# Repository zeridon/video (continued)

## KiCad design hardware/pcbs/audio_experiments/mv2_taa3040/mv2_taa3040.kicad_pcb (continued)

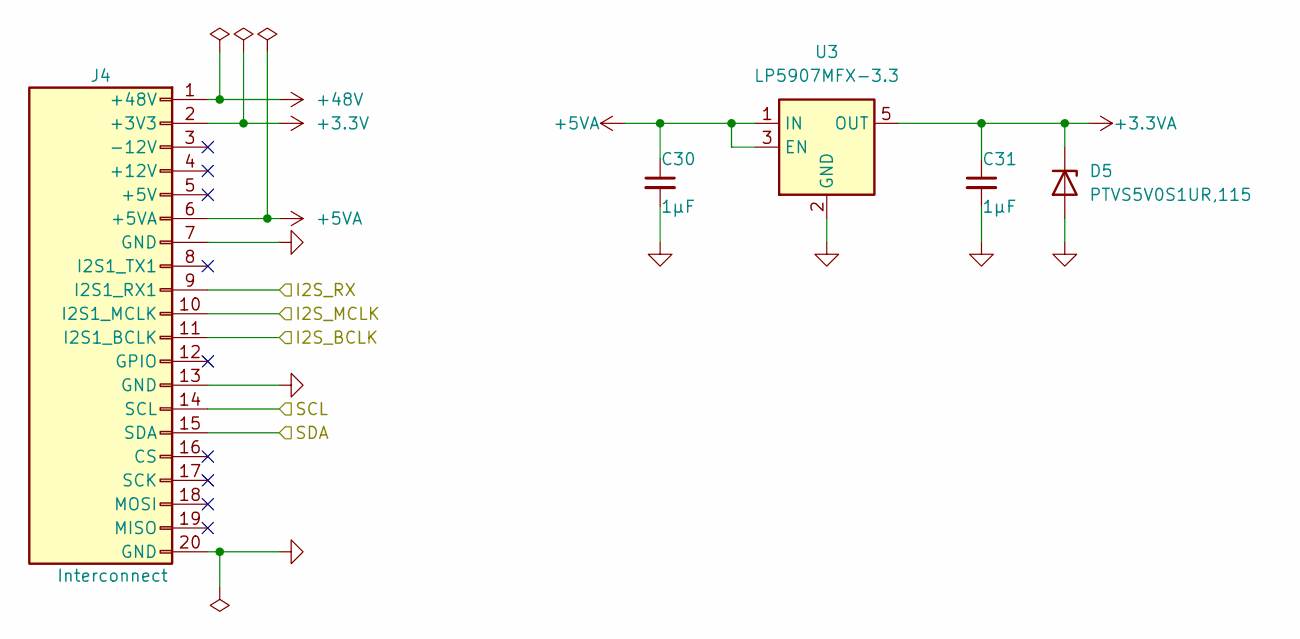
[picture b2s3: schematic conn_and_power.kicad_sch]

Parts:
C30, C31: 1μF; C_0805_2012Metric; MPN C 1μF 16V 0805
D5: PTVS5V0S1UR,115; Nexperia_CFP3_SOD-123W; MPN PTVS5V0S1UR,115; LCSC C478011
J4: Interconnect; PinHeader_1x20_P2.54mm_Vertical; MPN Header_1x20
U3: LP5907MFX-3.3; SOT-23-5; MPN LP5907MFX-3.3; LCSC C80670

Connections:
+3.3V: J4.2 (+3V3); also elsewhere on the board
+3.3VA: C31.1, D5.1 (K), U3.5 (OUT); also elsewhere on the board
+5VA: C30.1, J4.6 (+5VA), U3.1 (IN), U3.3 (EN)
+48V: J4.1 (+48V); also elsewhere on the board
/Conn and power/I2S_BCLK: J4.11 (I2S1_BCLK); also elsewhere on the board
/Conn and power/I2S_MCLK: J4.10 (I2S1_MCLK); also elsewhere on the board
/Conn and power/I2S_RX: J4.9 (I2S1_RX1); also elsewhere on the board
/Conn and power/SCL: J4.14 (SCL); also elsewhere on the board
/Conn and power/SDA: J4.15 (SDA); also elsewhere on the board
GND: C30.2, C31.2, D5.2 (A), J4.7 (GND), J4.13 (GND), J4.20 (GND), U3.2 (GND); also elsewhere on the board

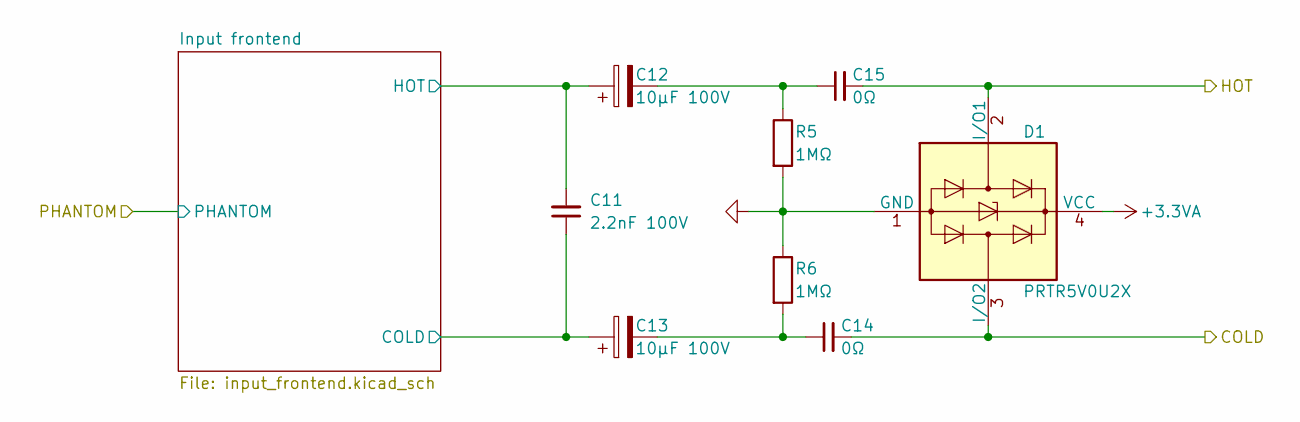
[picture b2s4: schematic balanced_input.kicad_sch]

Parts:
C11: 2.2nF 100V; C_0805_2012Metric; MPN C 2.2nF 100V 0805
C12, C13: 10μF 100V; CP_Radial_D5.0mm_P2.00mm; MPN C 10μF 100V P2
C14: 0Ω; C_1206_3216Metric; MPN R 0Ω 1206
C15: 0Ω; C_1206_3216Metric; MPN R 0Ω 0805
D1: PRTR5V0U2X; SOT-143; MPN PRTR5V0U2X,215; LCSC C12333
R5, R6: 1MΩ; R_0603_1608Metric; MPN 1MΩ 125mW 5% 0603

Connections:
+3.3VA: D1.4 (VCC); also elsewhere on the board
/Balanced Input 1/COLD: C14.2, D1.3 (I/O2); also elsewhere on the board
/Balanced Input 1/HOT: C15.2, D1.2 (I/O1); also elsewhere on the board
/Balanced Input 1/Input frontend/COLD: C11.1, C13.1; also elsewhere on the board
/Balanced Input 1/Input frontend/HOT: C11.2, C12.1; also elsewhere on the board
GND: D1.1 (GND), R5.2, R6.1; also elsewhere on the board
unnamed: C12.2, C15.1, R5.1
unnamed: C13.2, C14.1, R6.2

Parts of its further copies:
C16: 2.2nF 100V; C_0805_2012Metric; MPN C 2.2nF 100V 0805
C17, C18: 10μF 100V; CP_Radial_D5.0mm_P2.00mm; MPN C 10μF 100V P2
C19: 0Ω; C_1206_3216Metric; MPN R 0Ω 1206
C20: 0Ω; C_1206_3216Metric; MPN R 0Ω 0805
D2: PRTR5V0U2X; SOT-143; MPN PRTR5V0U2X,215; LCSC C12333
R7, R8: 1MΩ; R_0603_1608Metric; MPN 1MΩ 125mW 5% 0603

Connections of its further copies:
+3.3VA: D2.4 (VCC); also elsewhere on the board
/Balanced Input 2/COLD: C19.2, D2.3 (I/O2); also elsewhere on the board
/Balanced Input 2/HOT: C20.2, D2.2 (I/O1); also elsewhere on the board
/Balanced Input 2/Input frontend/COLD: C16.1, C18.1; also elsewhere on the board
/Balanced Input 2/Input frontend/HOT: C16.2, C17.1; also elsewhere on the board
GND: D2.1 (GND), R7.2, R8.1; also elsewhere on the board
unnamed: C17.2, C20.1, R7.1
unnamed: C18.2, C19.1, R8.2

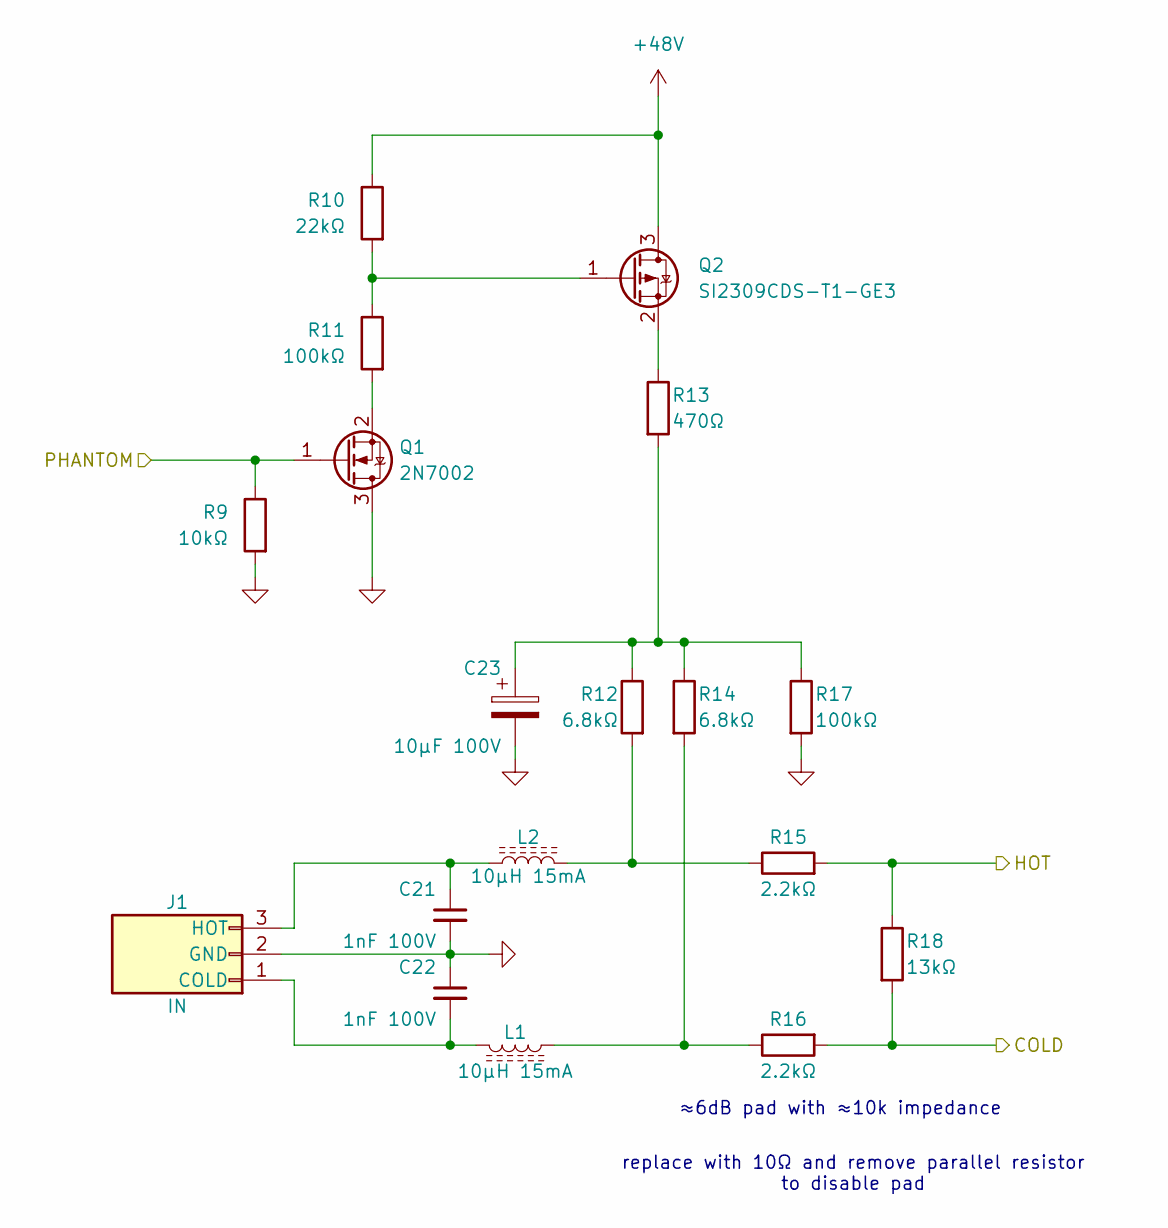
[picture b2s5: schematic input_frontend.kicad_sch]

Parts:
C21, C22: 1nF 100V; C_0805_2012Metric; MPN C 1nF 100V 0805
C23: 10μF 100V; CP_Radial_D5.0mm_P2.00mm; MPN C 10μF 100V P2
J1: MTA100-3; mta100_01x3_P2.54_640455-3; MPN 640457-3
L1, L2: 10μH 15mA; L_0805_2012Metric; MPN SDFL1608S100KTF or LQM21FN100N00L; LCSC C1046
Q1: 2N7002; SOT-23; Part 2N7002; LCSC C8545
Q2: SI2309CDS-T1-GE3; SOT-23; MPN SI2309CDS-T1-GE3
R9: 10kΩ; R_0603_1608Metric; MPN R 10kΩ 125mW 5% 0603
R10: 22kΩ; R_0603_1608Metric; MPN R 22kΩ 125mW 5% 0603
R11, R17: 100kΩ; R_0603_1608Metric; MPN R 100kΩ 125mW 5% 0603
R12, R14: 6.8kΩ; R_0603_1608Metric; MPN R 6.8kΩ 125mW 1% 0603
R13: 470Ω; R_0603_1608Metric; MPN R 470Ω 125mW 5% 0603
R15, R16: 2.2kΩ; R_0603_1608Metric; MPN R 2.2kΩ 125mW 1% 0603
R18: 13kΩ; R_0603_1608Metric; MPN R 13kΩ 125mW 1% 0603

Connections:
+48V: Q2.3 (D), R10.1; also elsewhere on the board
/Balanced Input 3/Input frontend/COLD: R16.2, R18.2; also elsewhere on the board
/Balanced Input 3/Input frontend/HOT: R15.2, R18.1; also elsewhere on the board
/Balanced Input 3/PHANTOM: Q1.1 (G), R9.1; also elsewhere on the board
GND: C21.2, C22.1, C23.2, J1.2, Q1.3 (D), R9.2, R17.2; also elsewhere on the board
unnamed: C23.1, R12.1, R13.2, R14.1, R17.1
unnamed: C22.2, J1.1, L1.1
unnamed: C21.1, J1.3, L2.1
unnamed: L1.2, R14.2, R16.1
unnamed: L2.2, R12.2, R15.1
unnamed: Q1.2 (S), R11.2
unnamed: Q2.1 (G), R10.2, R11.1
unnamed: Q2.2 (S), R13.1

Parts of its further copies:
C24, C25, C27, C28, C32, C33: 1nF 100V; C_0805_2012Metric; MPN C 1nF 100V 0805
C26, C29, C34: 10μF 100V; CP_Radial_D5.0mm_P2.00mm; MPN C 10μF 100V P2
J2, J3, J5: MTA100-3; mta100_01x3_P2.54_640455-3; MPN 640457-3
L3, L4, L5, L6, L7, L8: 10μH 15mA; L_0805_2012Metric; MPN SDFL1608S100KTF or LQM21FN100N00L; LCSC C1046
Q3, Q5, Q7: 2N7002; SOT-23; Part 2N7002; LCSC C8545
Q4, Q6, Q8: SI2309CDS-T1-GE3; SOT-23; MPN SI2309CDS-T1-GE3
R19, R29, R39: 10kΩ; R_0603_1608Metric; MPN R 10kΩ 125mW 5% 0603
R20, R30, R40: 22kΩ; R_0603_1608Metric; MPN R 22kΩ 125mW 5% 0603
R21, R27, R31, R37, R41, R47: 100kΩ; R_0603_1608Metric; MPN R 100kΩ 125mW 5% 0603
R22, R24, R32, R34, R42, R44: 6.8kΩ; R_0603_1608Metric; MPN R 6.8kΩ 125mW 1% 0603
R23, R33, R43: 470Ω; R_0603_1608Metric; MPN R 470Ω 125mW 5% 0603
R25, R26, R35, R36, R45, R46: 2.2kΩ; R_0603_1608Metric; MPN R 2.2kΩ 125mW 1% 0603
R28, R38, R48: 13kΩ; R_0603_1608Metric; MPN R 13kΩ 125mW 1% 0603

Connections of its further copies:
+48V: Q4.3 (D), Q6.3 (D), Q8.3 (D), R20.1, R30.1, R40.1; also elsewhere on the board
/Balanced Input 1/Input frontend/COLD: R46.2, R48.2; also elsewhere on the board
/Balanced Input 1/Input frontend/HOT: R45.2, R48.1; also elsewhere on the board
/Balanced Input 1/PHANTOM: Q7.1 (G), R39.1; also elsewhere on the board
/Balanced Input 2/Input frontend/COLD: R26.2, R28.2; also elsewhere on the board
/Balanced Input 2/Input frontend/HOT: R25.2, R28.1; also elsewhere on the board
/Balanced Input 2/PHANTOM: Q3.1 (G), R19.1; also elsewhere on the board
/Balanced Input 4/Input frontend/COLD: R36.2, R38.2; also elsewhere on the board
/Balanced Input 4/Input frontend/HOT: R35.2, R38.1; also elsewhere on the board
/Balanced Input 4/PHANTOM: Q5.1 (G), R29.1; also elsewhere on the board
GND: C24.2, C25.1, C26.2, C27.2, C28.1, C29.2, C32.2, C33.1, C34.2, J2.2, J3.2, J5.2, Q3.3 (D), Q5.3 (D), Q7.3 (D), R19.2, R27.2, R29.2, R37.2, R39.2, R47.2; also elsewhere on the board
unnamed: C26.1, R22.1, R23.2, R24.1, R27.1
unnamed: C29.1, R32.1, R33.2, R34.1, R37.1
unnamed: C34.1, R42.1, R43.2, R44.1, R47.1
unnamed: C25.2, J2.1, L3.1
unnamed: C24.1, J2.3, L4.1
unnamed: C28.2, J3.1, L5.1
unnamed: C27.1, J3.3, L6.1
unnamed: C33.2, J5.1, L7.1
unnamed: C32.1, J5.3, L8.1
unnamed: L3.2, R24.2, R26.1
unnamed: L4.2, R22.2, R25.1
unnamed: L5.2, R34.2, R36.1
unnamed: L6.2, R32.2, R35.1
unnamed: L7.2, R44.2, R46.1
unnamed: L8.2, R42.2, R45.1
unnamed: Q3.2 (S), R21.2
unnamed: Q4.1 (G), R20.2, R21.1
unnamed: Q4.2 (S), R23.1
unnamed: Q5.2 (S), R31.2
unnamed: Q6.1 (G), R30.2, R31.1
unnamed: Q6.2 (S), R33.1
unnamed: Q7.2 (S), R41.2
unnamed: Q8.1 (G), R40.2, R41.1
unnamed: Q8.2 (S), R43.1

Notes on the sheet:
≈6dB pad with ≈10k impedance
replace with 10Ω and remove parallel resistor to disable pad

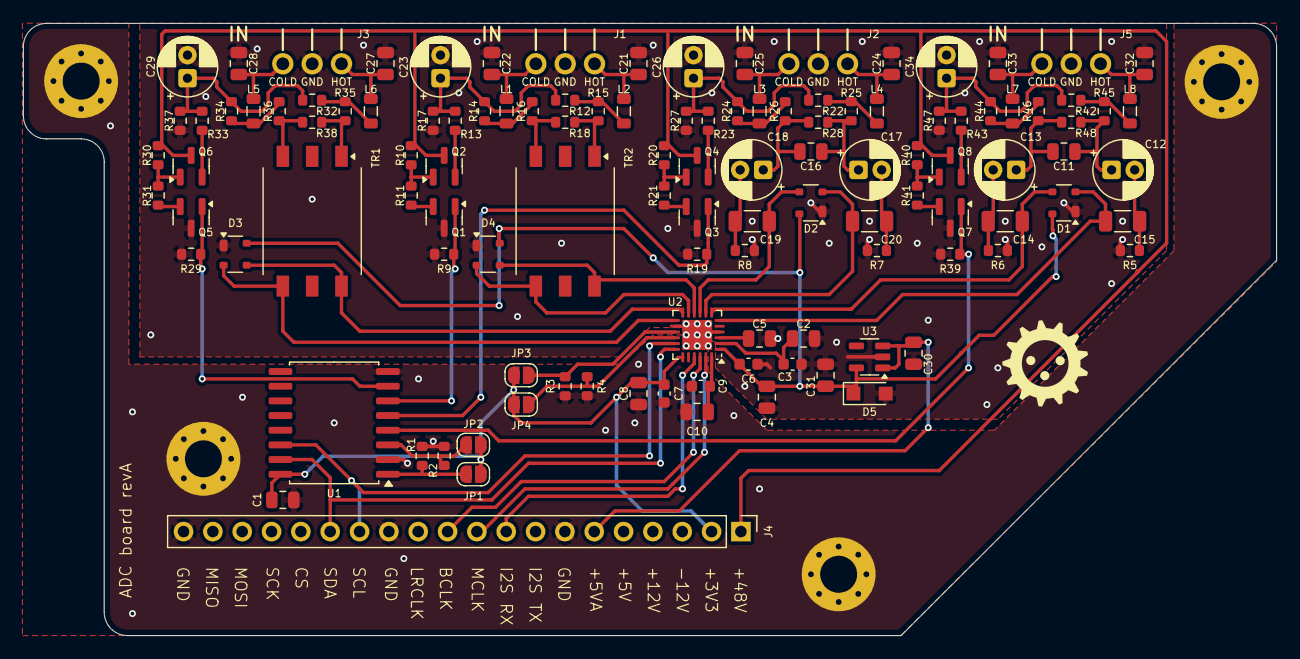
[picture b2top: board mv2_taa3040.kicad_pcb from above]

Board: 4 copper layers, 108.5 x 53.0 mm, 121 parts (0 on the bottom side), 73 nets.

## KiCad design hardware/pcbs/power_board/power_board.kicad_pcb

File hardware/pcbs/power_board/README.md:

## power board

This is a PCB with the following features:
- Passthrough, filtering and fusing of 12V power from the PSU
- GPIO passthrough and level shifting for:
    - PWM fans
    - Buttons with LEDs (or just buttons, or just LEDs) - like [this one](https://eu.mouser.com/ProductDetail/Shin-Chin/R13-508BL-05-BRR12V?qs=gZXFycFWdAOqSBZAzEyqbA%3D%3D)
- A temperature sensor
- USB3 passthrough
- External USBs with isolated grounds for charging, designed to be able to power Sennheiser AVX receivers

Internal connections:
- 1x 12V input (2-pin screw terminal), connects to PSU's 12V output
- 3x 12V outputs (2-pin screw terminals), one of which powers an SBC like the [Radxa X2L](https://radxa.com/products/x/x2l/), the others are spare
- 2x 5V outputs (2-pin screw terminals), for misc purposes
- 1x USB3-micro-B port for USB3 passthrough
- 1x 3-pin I²C header that connects to the SBC's GPIO
- 4x 4-pin fan connectors with pwm
- 4x 4-pin connectors for buttons-with-LEDs or leds (VDD-LED-BTN-VDD)

Panel components:
- 1x optional 12V input barrel connector, in case we use an external PSU
- 1x USB3-A passthrough port
- 4x USB2-A charging connectors

Proposed changes:
- make the fan connectors 4 instead of 5
- make the fan controller support 3-pin 5v fans instead of 4-pin 12v fans
- make the fan connectors be 3-pin screw terminals (now that I think of it, this is probably a bad idea... screw terminals are huge - maybe it's better to use molex connectors after all, but this would mean having to attach a male connector to every single fan, e.g. 600 of them - I'm not sure what the good tradeoff here is)
- remove the 3 software-controlled leds (but keep the extra gpio pin header)
- remove the 12V input connector, leave only the barrel jack
- remove all internal "spare power" connectors and replace them with a single header that has all voltages
- make the board in such a shape that it doesn't cover the hole that will be used for mounting the bracket
- outset the barrel connector a bit to the outside, since it's supposed to go through the front panel (as opposed to the USBs, which are supposed to be behind)

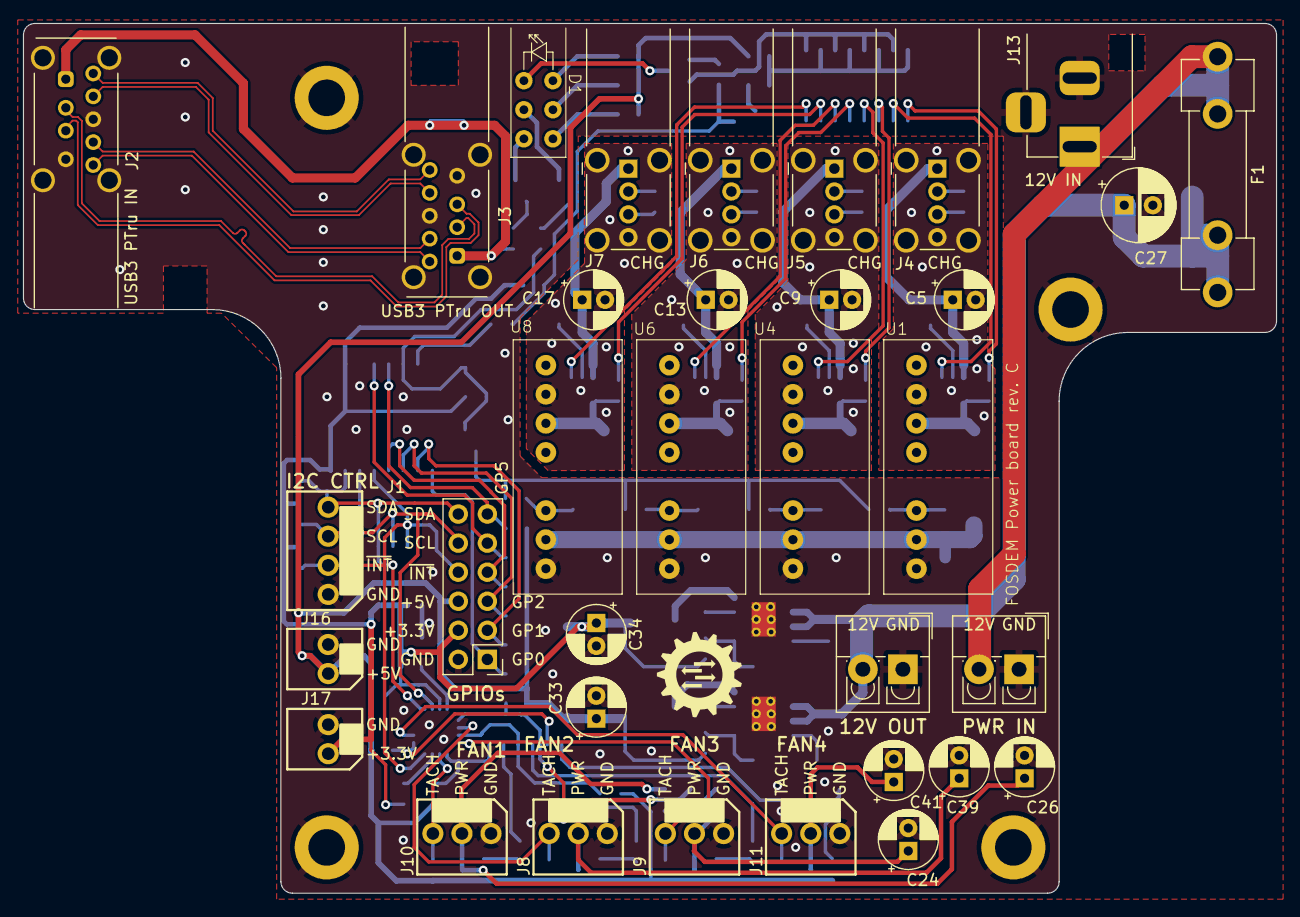
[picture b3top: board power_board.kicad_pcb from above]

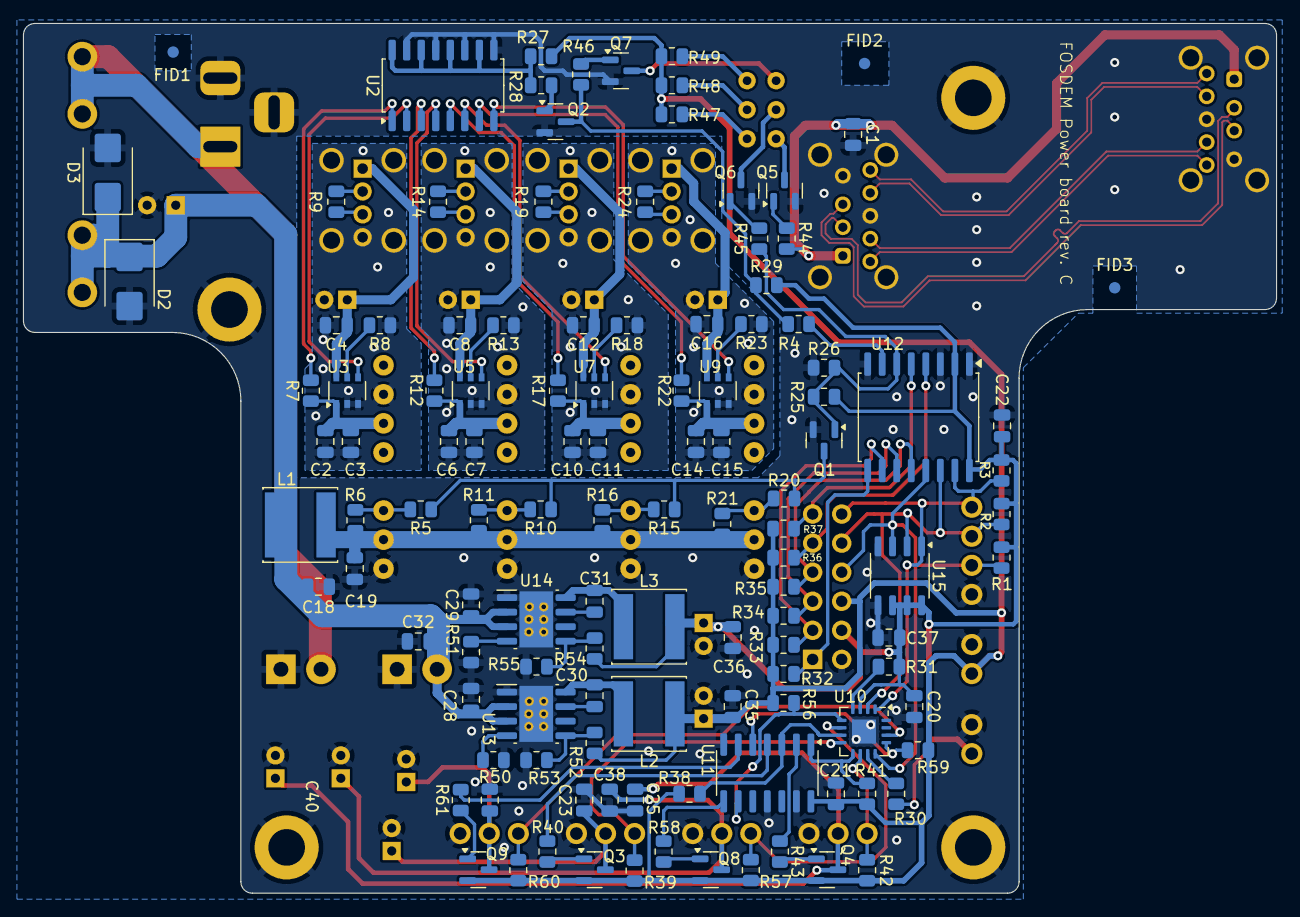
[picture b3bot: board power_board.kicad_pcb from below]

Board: 2 copper layers, 109.5 x 76.0 mm, 157 parts (119 on the bottom side), 103 nets.

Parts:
C1, C3, C4, C7, C8, C11, C12, C15, C16, C20, C22, C32, C35, C36: 1μF; C_0805_2012Metric
C2, C6, C10, C14, C18, C19, C21: 10μF; C_0805_2012Metric
C5, C9, C13, C17, C24, C26, C33, C34, C39, C41: 100μF; CP_Radial_D5.0mm_P2.00mm
C23, C25, C38, C40: 22μF; C_0805_2012Metric
C27: 220μF; CP_Radial_D6.3mm_P2.50mm
C28, C29, C30, C31, C37: 100nF; C_0805_2012Metric
D1: OSTSLT3E34X-3F3C
D2: S2A; D_SMB
D3: Zener 15V; D_SMB
F1: Fuse; Fuseholder_FS002
FID1, FID2, FID3: Fiducial; Fiducial_1mm_Mask2mm
H1, H2, H3, H4: MountingHole_Pad; MountingHole_3.2mm_M3_keepout
J1: Header_01x04; mta100_01x4_P2.54_647050-4
J2, J3: USB3_A; USB3_A_Amphenol_GSB3116344KHHR
J4, J5, J6, J7: USB_A; USB_A_Amphenol_GSB19111KEU
J8, J9, J10, J11: Header_01x03; mta100_01x3_P2.54_647050-3
J12: Header_02x06; PinHeader_2x06_P2.54mm_Vertical
J13: Barrel Jack; BarrelJack_Horizontal
J14, J15: ScrewTerminal_02; TerminalBlock_4Ucon_1x02_P3.50mm_Vertical
J16, J17: MTA100_02; mta100_01x2_P2.54_647050-2
L1: 22μH; L_Sunlord_SWPA6045S
L2, L3: 15μH; L_Changjiang_FNR6045S
Q1, Q2, Q5, Q6, Q7: BSS138; SOT-23
Q3, Q4, Q8, Q9: IRML6401; SOT-23
R1, R2, R3, R4, R25, R26, R29, R38, R41, R56, R59: 10kΩ; R_0805_2012Metric
R5, R10, R15, R20, R28, R40, R43, R44, R45, R46, R58, R61: 10Ω; R_0805_2012Metric
R6, R11, R16, R21, R32, R33, R34, R35, R36, R37: 100kΩ; R_0805_2012Metric
R7, R12, R17, R22, R27, R39, R42, R57, R60: 4.7kΩ; R_0805_2012Metric
R8, R13, R18, R23: 36kΩ; R_0805_2012Metric
R9, R14, R19, R24: 100Ω; R_0805_2012Metric
R30: 15kΩ; R_0805_2012Metric
R31: 33kΩ; R_0805_2012Metric
R47, R48, R49: 1.8kΩ; R_0805_2012Metric
R50, R51: 47kΩ; R_0805_2012Metric
R52: 30kΩ; R_0805_2012Metric
R53: 7.5kΩ; R_0805_2012Metric
R54: 31.6kΩ; R_0805_2012Metric
R55: 13.7kΩ; R_0805_2012Metric
U1, U4, U6, U8: VRB1205S-6WR3; VRBxxxx-6WR3
U2: LTV-247; SOP-16_4.4x10.4mm_P1.27mm
U3, U5, U7, U9: NCP380; TSOP-6_1.65x3.05mm_P0.95mm
U10: EMC2305; QFN-16-1EP_4x4mm_P0.65mm_EP2.1x2.1mm
U11: 4069; SO-14_3.9x8.65mm_P1.27mm
U12: TCA9534; SOIC-16W_7.5x10.3mm_P1.27mm
U13, U14: LMR38020; Texas_R-PDSO-G8_EP2.95x4.9mm_Mask2.4x3.1mm_ThermalVias
U15: TMP1075D; SO-8_3.9x4.9mm_P1.27mm

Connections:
+3.3V: C20.1, C22.1, C34.1, C36.1, C37.1, J12.4, J17.1, L3.2, R1.2, R2.2, R3.2, R25.2, R29.2, R30.2, R31.2, R54.2, U10.3 (VDD), U12.2 (A1), U12.16 (VDD), U15.6 (A1), U15.7 (A0), U15.8 (V+)
+5V: C21.1, C33.1, C35.1, J12.6, J16.1, L2.2, Q3.2 (S), Q4.2 (S), Q8.2 (S), Q9.2 (S), R27.2, R32.2, R33.2, R34.2, R35.2, R36.2, R37.2, R38.2, R39.2, R41.2, R42.2, R47.2, R48.2, R49.2, R52.2, R56.2, R57.2, R59.2, R60.2, U11.14 (VDD)
+12V: C18.1, C27.1, C28.1, C29.1, C32.1, D2.1 (K), D3.1 (K), F1.2, J15.2, L1.1, U13.2 (EN), U13.3 (VIN), U14.2 (EN), U14.3 (VIN)
/Fan Controller/Fan PWM 1/FAN_VDD: C38.1, C39.1, J8.2, Q8.3 (D)
/Fan Controller/Fan PWM 1/PWM: R56.1, U10.5 (PWM1), U11.9
/Fan Controller/Fan PWM 1/TACH_IN: J8.3, R57.1, U10.6 (TACH1)
/Fan Controller/Fan PWM 2/FAN_VDD: C23.1, C24.1, J9.2, Q3.3 (D)
/Fan Controller/Fan PWM 2/PWM: R38.1, U10.7 (PWM2), U11.3
/Fan Controller/Fan PWM 2/TACH_IN: J9.3, R39.1, U10.8 (TACH2)
/Fan Controller/Fan PWM 3/FAN_VDD: C25.1, C26.1, J10.2, Q4.3 (D)
/Fan Controller/Fan PWM 3/PWM: R41.1, U10.9 (PWM3), U11.1
/Fan Controller/Fan PWM 3/TACH_IN: J10.3, R42.1, U10.10 (TACH3)
/Fan Controller/Fan PWM 4/FAN_VDD: C40.1, C41.1, J11.2, Q9.3 (D)
/Fan Controller/Fan PWM 4/PWM: R59.1, U10.13 (PWM4), U11.5
/Fan Controller/Fan PWM 4/TACH_IN: J11.3, R60.1, U10.14 (TACH4)
/Fan Controller/SCL: J1.3, J12.10, R2.1, U10.2 (SMCLK), U12.14 (SCL), U15.2 (SCL)
/Fan Controller/SDA: J1.4, J12.12, R3.1, U10.1 (SMDATA), U12.15 (SDA), U15.1 (SDA)
/Fan Controller/~ALERT: J1.2, J12.8, R1.1, U10.12 (~ALERT), U12.13 (~INT), U15.3 (ALERT)
/GPIOs/GP0: J12.9, R36.1, U12.4 (P0)
/GPIOs/GP1: J12.7, R35.1, U12.12 (P7)
/GPIOs/GP2: J12.1, R32.1, U12.9 (P4)
/GPIOs/GP3: J12.3, R33.1, U12.10 (P5)
/GPIOs/GP4: J12.5, R34.1, U12.11 (P6)
/GPIOs/GP5: J12.11 (Pin_9), R37.1, U12.5 (P1)
/GPIOs/GPIO6: Q1.1 (G), R25.1, R26.2, R45.1, U12.6 (P2)
/GPIOs/GPIO7: R4.2, U12.7 (P3)
/Indicator LEDs/OVERLOAD: Q2.3 (D), R4.1, R29.1, R46.1
/Isolated chargers/Isolated charger 1/GND-CHG: C2.2, C3.2, C4.2, C5.2, J4.4 (GND), J4.5 (Shield), R8.1, U1.7 (OGND), U3.2 (GND), U3.3 (EN)
/Isolated chargers/Isolated charger 1/VIN: C19.1, L1.2, R6.1, R11.1, R16.1, R21.1, U1.2 (VIN), U4.2 (VIN), U6.2 (VIN), U8.2 (VIN)
/Isolated chargers/Isolated charger 1/~EN: Q1.3 (D), R5.1, R10.1, R15.1, R20.1
/Isolated chargers/Isolated charger 1/~OVERCURRENT: R27.1, R28.1, U2.10, U2.12, U2.14, U2.16
/Isolated chargers/Isolated charger 2/GND-CHG: C10.2, C11.2, C12.2, C13.2, J6.4 (GND), J6.5 (Shield), R18.1, U6.7 (OGND), U7.2 (GND), U7.3 (EN)
/Isolated chargers/Isolated charger 3/GND-CHG: C14.2, C15.2, C16.2, C17.2, J7.4 (GND), J7.5 (Shield), R23.1, U8.7 (OGND), U9.2 (GND), U9.3 (EN)
/Isolated chargers/Isolated charger 4/GND-CHG: C6.2, C7.2, C8.2, C9.2, J5.4 (GND), J5.5 (Shield), R13.1, U4.7 (OGND), U5.2 (GND), U5.3 (EN)
/Power supply/FB3V3: R54.1, R55.2, U14.5 (FB)
/Power supply/FB5V: R52.1, R53.2, U13.5 (FB)
/USB Passthrough/D+: J2.3 (D+), J3.3 (D+)
/USB Passthrough/D-: J2.2 (D-), J3.2 (D-)
/USB Passthrough/SSRX+: J2.6 (SSRX+), J3.8 (SSTX-)
/USB Passthrough/SSRX-: J2.5 (SSRX-), J3.9 (SSTX+)
/USB Passthrough/SSTX+: J2.9 (SSTX+), J3.5 (SSRX-)
/USB Passthrough/SSTX-: J2.8 (SSTX-), J3.6 (SSRX+)
/USB Passthrough/VBus: C1.1, J2.1 (VBUS), J3.1 (VBUS), R44.1
GND: C1.2, C18.2, C19.2, C20.2, C21.2, C22.2, C23.2, C24.2, C25.2, C26.2, C27.2, C28.2, C29.2, C32.2, C33.2, C34.2, C35.2, C36.2, C37.2, C38.2, C39.2, C40.2, C41.2, D2.2 (A), D3.2 (A), H1.1, H2.1, H3.1, H4.1, J1.1, J2.4 (GND), J2.7 (DRAIN), J2.10 (SHIELD), J3.4 (GND), J3.7 (DRAIN), J3.10 (SHIELD), J8.1, J9.1, J10.1, J11.1, J12.2, J13.2, J13.3, J14.1, J15.1, J16.2, J17.2, Q1.2 (S), Q2.2 (S), Q5.2 (S), Q6.2 (S), Q7.2 (S), R26.1, R50.1, R51.1, R53.1, R55.1, U1.1 (IGND), U2.9, U2.11, U2.13, U2.15, U4.1 (IGND), U6.1 (IGND), U8.1 (IGND), U10.17 (GND), U11.7 (VSS), U11.11, U11.13, U12.1 (A0), U12.3 (A2), U12.8 (GND), U13.1 (PGND), U13.9 (PAD), U14.1 (PGND), U14.9 (PAD), U15.4 (GND), U15.5 (A2)
unnamed: D1.5 (GA), R47.1
unnamed: D1.6 (GK), Q5.3 (D)
unnamed: D1.1 (RA), R49.1
unnamed: D1.2 (RK), Q7.3 (D)
unnamed: D1.3 (YA), R48.1
unnamed: D1.4 (YK), Q6.3 (D)
unnamed: J4.3 (D+), R9.2
unnamed: J4.2 (D-), R9.1
unnamed: C4.1, C5.1, J4.1 (VBUS), U3.6 (OUT)
unnamed: J5.3 (D+), R14.2
unnamed: J5.2 (D-), R14.1
unnamed: C8.1, C9.1, J5.1 (VBUS), U5.6 (OUT)
unnamed: J6.3 (D+), R19.2
unnamed: J6.2 (D-), R19.1
unnamed: C12.1, C13.1, J6.1 (VBUS), U7.6 (OUT)
unnamed: J7.3 (D+), R24.2
unnamed: J7.2 (D-), R24.1
unnamed: C16.1, C17.1, J7.1 (VBUS), U9.6 (OUT)
unnamed: F1.1, J13.1, J14.2
unnamed: Q2.1 (G), R28.2
unnamed: Q3.1 (G), R40.2
unnamed: Q4.1 (G), R43.2
unnamed: Q5.1 (G), R44.2
unnamed: Q6.1 (G), R45.2
unnamed: Q7.1 (G), R46.2
unnamed: Q8.1 (G), R58.2
unnamed: Q9.1 (G), R61.2
unnamed: R7.1, U2.1
unnamed: R12.1, U2.3
unnamed: R17.1, U2.5
unnamed: R22.1, U2.7
unnamed: R40.1, U11.4
unnamed: R43.1, U11.2
unnamed: R58.1, U11.8
unnamed: R61.1, U11.6
unnamed: R5.2, R6.2, U1.3 (EN)
unnamed: C2.1, C3.1, R7.2, U1.6 (VOUT), U3.1 (IN)
unnamed: R8.2, U3.5 (ILIM)
unnamed: U2.2, U3.4 (~FLAG)
unnamed: R10.2, R11.2, U4.3 (EN)
unnamed: C6.1, C7.1, R12.2, U4.6 (VOUT), U5.1 (IN)
unnamed: R13.2, U5.5 (ILIM)
unnamed: U2.4, U5.4 (~FLAG)
unnamed: R15.2, R16.2, U6.3 (EN)
unnamed: C10.1, C11.1, R17.2, U6.6 (VOUT), U7.1 (IN)
unnamed: R18.2, U7.5 (ILIM)
unnamed: U2.6, U7.4 (~FLAG)
unnamed: R20.2, R21.2, U8.3 (EN)
unnamed: C14.1, C15.1, R22.2, U8.6 (VOUT), U9.1 (IN)
unnamed: R23.2, U9.5 (ILIM)
unnamed: U2.8, U9.4 (~FLAG)
unnamed: R31.1, U10.4 (ADDR_SEL)
unnamed: R30.1, U10.11 (CLK)
unnamed: C30.1, U13.7 (BOOT)
unnamed: R50.2, U13.4 (RT/SYNC)
unnamed: C30.2, L2.1, U13.8 (SW)
unnamed: C31.1, U14.7 (BOOT)
unnamed: R51.2, U14.4 (RT/SYNC)
unnamed: C31.2, L3.1, U14.8 (SW)

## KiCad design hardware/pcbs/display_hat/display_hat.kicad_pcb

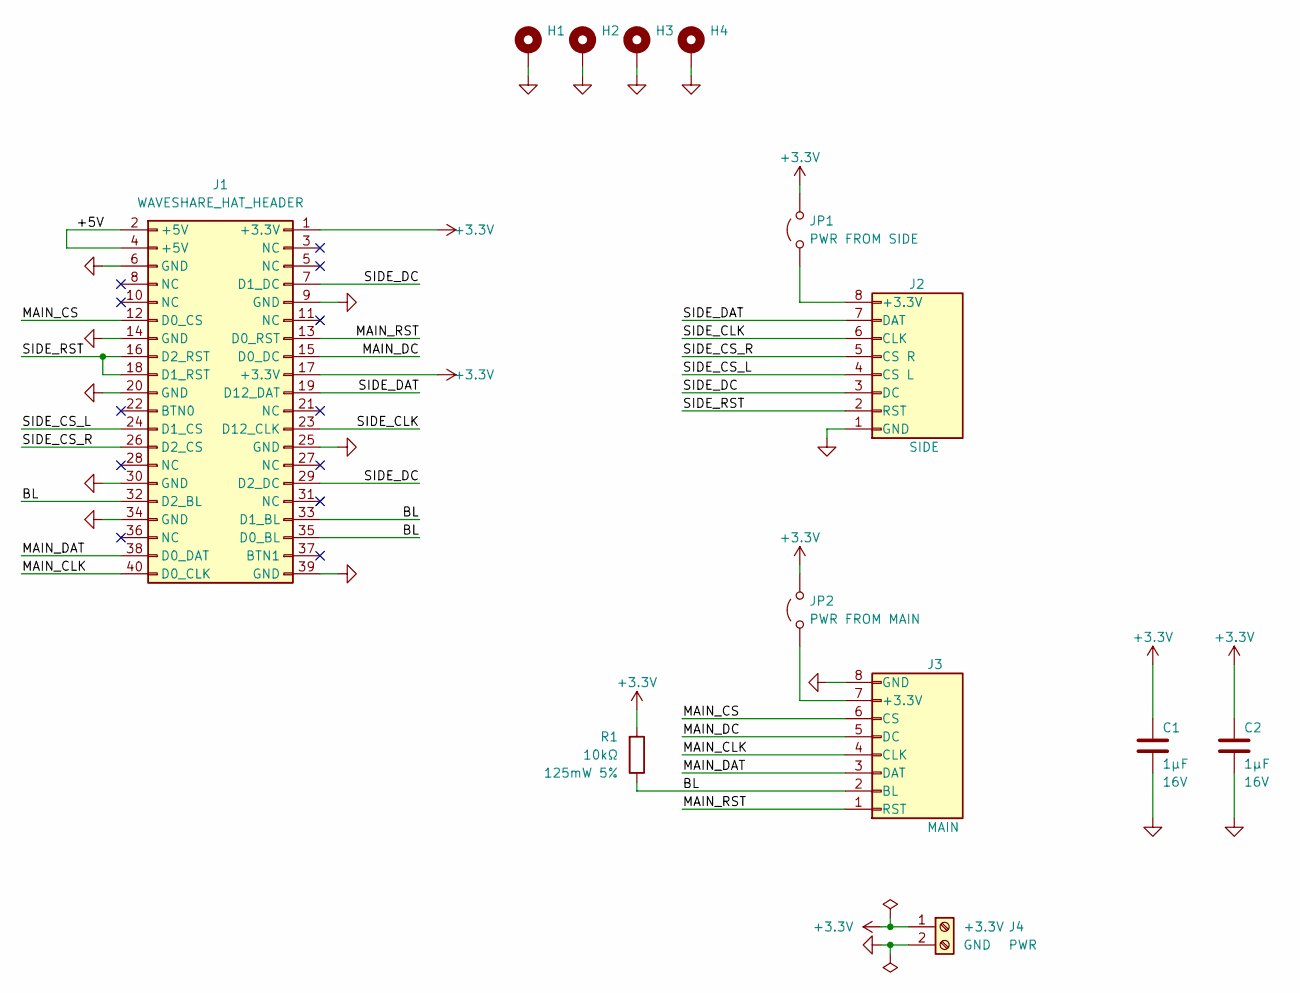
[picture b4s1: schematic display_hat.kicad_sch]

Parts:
C1, C2: 1μF; C_0805_2012Metric; Part C 1μF 16V 0805; LCSC C28323
H1, H2, H3, H4: MountingHole_Pad; MountingHole_2.2mm_M2_ISO7380_Pad
J1: WAVESHARE_HAT_HEADER; PinHeader_2x20_P2.54mm_Vertical; Part Header_2x20
J2, J3: MTA100_08; mta100_01x8_P2.54_640455-8; Part 640457-8
J4: MTA100_02; mta100_01x2_P2.54_640455-2; Part 640457-2
JP1: PWR FROM SIDE; PinHeader_1x02_P2.54mm_Horizontal; Part Header_Angled_2
JP2: PWR FROM MAIN; PinHeader_1x02_P2.54mm_Horizontal; Part Header_Angled_2
R1: 10kΩ; R_0805_2012Metric; Part R 10kΩ 125mW 5% 0805; LCSC C17414

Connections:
+3.3V: C1.1, C2.1, J1.1 (+3.3V), J1.17 (+3.3V), J4.1, JP1.1 (A), JP2.1 (A), R1.2
/+5V: J1.2 (+5V), J1.4 (+5V)
/BL: J1.32 (D2_BL), J1.33 (D1_BL), J1.35 (D0_BL), J3.2, R1.1
/MAIN_CLK: J1.40 (D0_CLK), J3.4
/MAIN_CS: J1.12 (D0_CS), J3.6
/MAIN_DAT: J1.38 (D0_DAT), J3.3
/MAIN_DC: J1.15 (D0_DC), J3.5
/MAIN_RST: J1.13 (D0_RST), J3.1
/SIDE_CLK: J1.23 (D12_CLK), J2.6
/SIDE_CS_L: J1.24 (D1_CS), J2.4
/SIDE_CS_R: J1.26 (D2_CS), J2.5
/SIDE_DAT: J1.19 (D12_DAT), J2.7
/SIDE_DC: J1.7 (D1_DC), J1.29 (D2_DC), J2.3
/SIDE_RST: J1.16 (D2_RST), J1.18 (D1_RST), J2.2
GND: C1.2, C2.2, H1.1, H2.1, H3.1, H4.1, J1.6 (GND), J1.9 (GND), J1.14 (GND), J1.20 (GND), J1.25 (GND), J1.30 (GND), J1.34 (GND), J1.39 (GND), J2.1, J3.8, J4.2
unnamed: J2.8, JP1.2 (B)
unnamed: J3.7, JP2.2 (B)

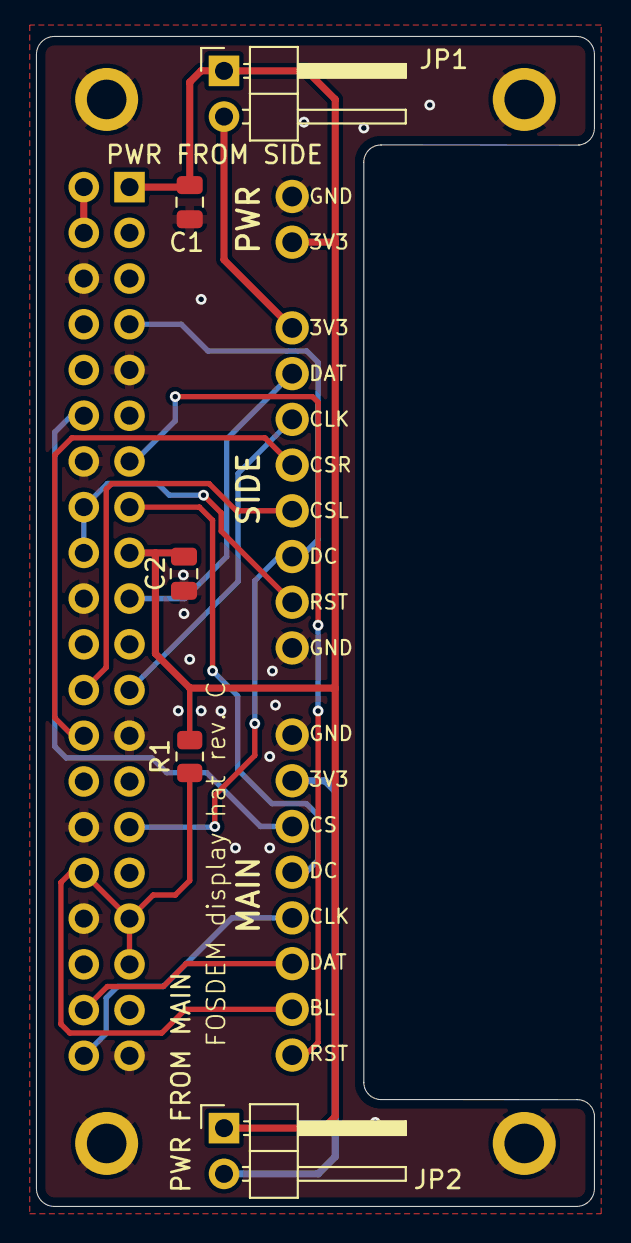
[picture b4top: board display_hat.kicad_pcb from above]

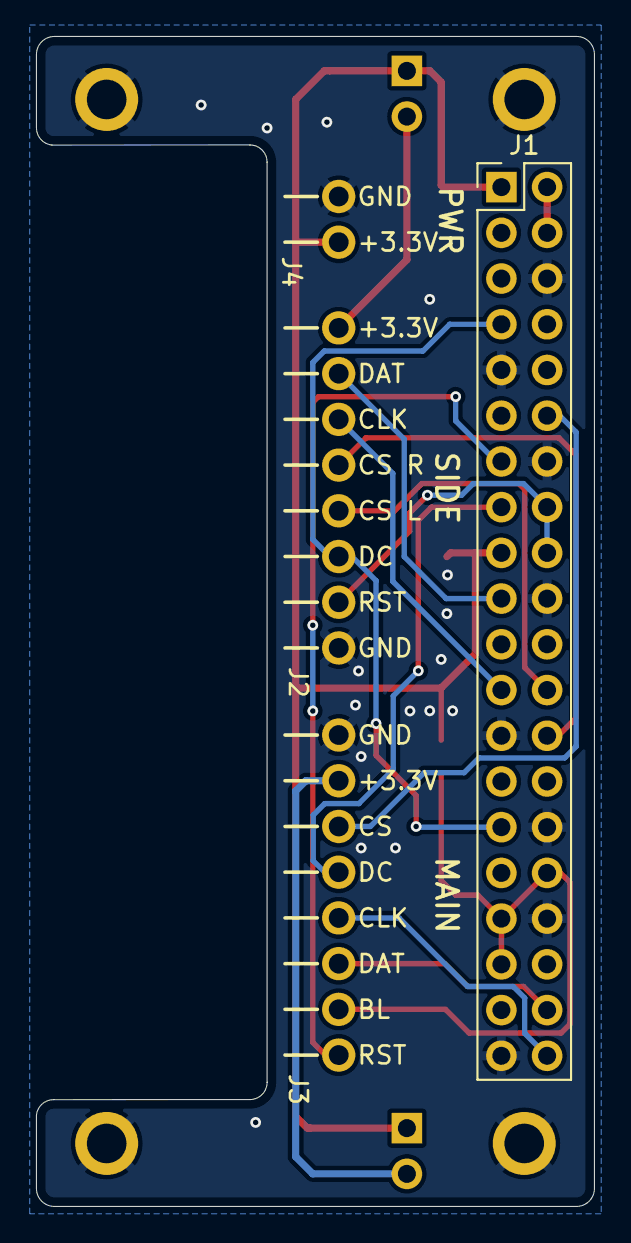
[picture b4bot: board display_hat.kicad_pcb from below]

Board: 2 copper layers, 31.0 x 65.0 mm, 13 parts (4 on the bottom side), 17 nets.

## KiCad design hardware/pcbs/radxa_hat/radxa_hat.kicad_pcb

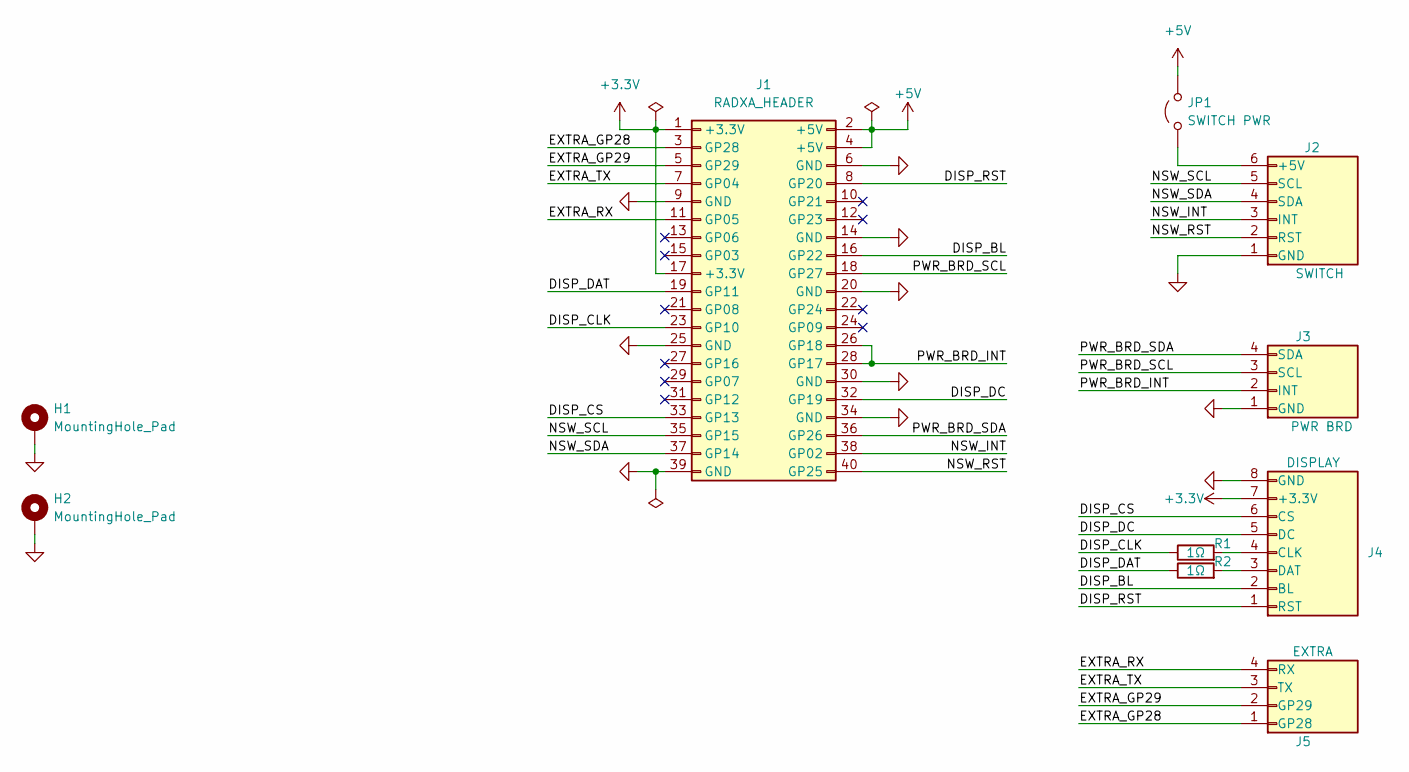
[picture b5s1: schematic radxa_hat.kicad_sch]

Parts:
H1, H2: MountingHole_Pad; MountingHole_3.2mm_M3_DIN965_Pad
J1: RADXA_HEADER; PinSocket_2x20_P2.54mm_Vertical; Part HeaderSocket_2x20
J2: Header_01x06; mta100_01x6_P2.54_640455-6; Part 640457-6
J3, J5: Header_01x04; mta100_01x4_P2.54_640455-4; Part 640457-4
J4: Header_01x08; mta100_01x8_P2.54_640455-8; Part 640457-8
JP1: SWITCH PWR; PinHeader_1x02_P2.54mm_Vertical; Part Header_Angled_2
R1, R2: 1Ω; R_0805_2012Metric; Part R 1Ω 125mW 1% 0805

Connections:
+3.3V: J1.1 (+3.3V), J1.17 (+3.3V), J4.7
+5V: J1.2 (+5V), J1.4 (+5V), JP1.2 (B)
/DISP_BL: J1.16 (GP22), J4.2
/DISP_CLK: J1.23 (GP10), R1.1
/DISP_CS: J1.33 (GP13), J4.6
/DISP_DAT: J1.19 (GP11), R2.1
/DISP_DC: J1.32 (GP19), J4.5
/DISP_RST: J1.8 (GP20), J4.1
/EXTRA_GP28: J1.3 (GP28), J5.1
/EXTRA_GP29: J1.5 (GP29), J5.2
/EXTRA_RX: J1.11 (GP05), J5.4
/EXTRA_TX: J1.7 (GP04), J5.3
/NSW_INT: J1.38 (GP02), J2.3
/NSW_RST: J1.40 (GP25), J2.2
/NSW_SCL: J1.35 (GP15), J2.5
/NSW_SDA: J1.37 (GP14), J2.4
/PWR_BRD_INT: J1.26 (GP18), J1.28 (GP17), J3.2
/PWR_BRD_SCL: J1.18 (GP27), J3.3
/PWR_BRD_SDA: J1.36 (GP26), J3.4
GND: H1.1, H2.1, J1.6 (GND), J1.9 (GND), J1.14 (GND), J1.20 (GND), J1.25 (GND), J1.30 (GND), J1.34 (GND), J1.39 (GND), J2.1, J3.1, J4.8
unnamed: J2.6, JP1.1 (A)
unnamed: J4.3, R2.2
unnamed: J4.4, R1.2

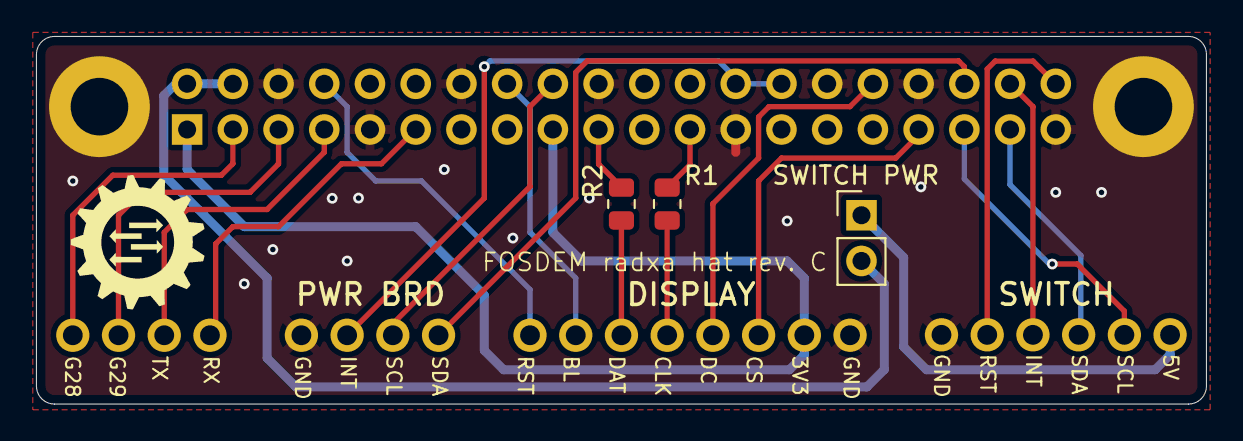
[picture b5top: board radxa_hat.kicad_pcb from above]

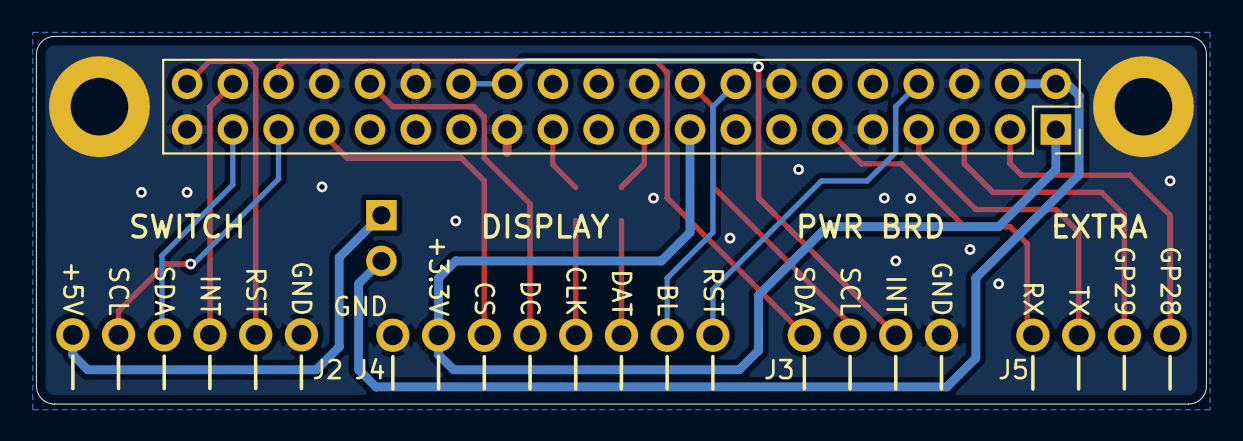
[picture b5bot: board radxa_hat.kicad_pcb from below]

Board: 2 copper layers, 65.0 x 20.4 mm, 10 parts (5 on the bottom side), 23 nets.
